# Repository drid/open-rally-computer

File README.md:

# Open Rally Computer

An open source tripmaster for navigation rallies

## Description

The Open Rally Computer (previously known as [Baja Pro](https://baja.matto.io/)) is a complete tripmaster for navigation rallies.

Some of its features are:

- Based on GPS technology
- Adjustable partial distance odometer
- Total distance odometer
- Speedometer
- Average speed
- Max speed
- Trip time
- Compass (CAP heading)
- Multiple languages and unit systems
- Firmware updates over-the-air

The main goal of this project is to achieve a widely used open-source device that can be improved over time by ourselves, the pilots behind the roadbook.

You can read a detailed writeup of the project here:

- [English version](https://matto.io/open-sourcing-the-baja-pro/)
- [Spanish version](https://matto.io/liberando-el-codigo-del-baja-pro/)

## Schematics and PCB

You can find all the necessary information for fabricating your own copy of the Open Rally Computer PCB in the [pcb](docs/pcb) and [schematics](docs/schematics) folders of this repository.

> **HELP NEEDED**: My knowledge in electronics is self-taught, so I'm sure there are quite a few improvements to be done in this department. If you know electronics and spot something that can be improved, please let me know by opening an issue.

- Previous models of this device have been fabricated at [JLCPCB](https://jlcpcb.com/) with great results and very good prices.
- The system I used to create the PCB was [EasyEDA](https://easyeda.com/). You can find files for the schematics and the PCB in their relative folders. There are also versions for Altium Designer.

> **HELP NEEDED**: I'd like to port these schematics and PCB to KiCad, so we continue with the open source spirit :)
>
> If you know your way around KiCad, I'd really appreciate some help porting this board.

The bill of materials is located in a CSV file in the [bom](docs/pcb/bom) folder. If you find a missing component, please report it by opening an issue.

## User manual

You can find a PDF version of the User Manual in the [manual](docs/manual) folder.

> **HELP NEEDED**: The user manual is currently only in Spanish and it still has a lot of Baja Pro branding that has to be changed to "Open Rally Computer". I'd really appreciate some help transcribing it to Markdown and translating it into other languages, being english the top priority right now.

## Getting Started

These instructions will allow you to compile the project in you local computer. In order to run it you will need an actual device.

### Prerequisites

This project has been developed using VSCode with the PlatformIO plugin, which is is the recommended setup.

- Install [VSCode](https://code.visualstudio.com/)
- Install the [PlatformIO plugin](https://platformio.org/install/ide?install=vscode)
- Clone this repository

```bash
git clone https://github.com/mattogodoy/open-rally-computer.git
```

### Building

To build this project you can open the directory of the repository you just downloaded in VSCode.

Once open, go to the sidebar at the left, PlatformIO -> esp32dev -> General -> Build

The required libraries are already bundled in the `lib` directory of this repo. PlatformIO will automatically try to use them.
If for some reason you are getting compilation errors because of missing libraries, you can always install them manually going to PlatformIO -> PIO Home -> Libraries.

You can find the list of necessary libraries in the file [platformio.ini](platformio.ini).

## Flashing into device

Once the project compiles correctly in your computer, you are ready to flash it into the rally computer.

1. Connect your ESP32 (DevKit or programmer) to your computer via USB.
2. Go to PlatformIO -> esp32dev -> General -> Upload
3. PlatformIO should automatically detect the serial port where your ESP32 is connected, buld the project and flash it for you.

## Contributing

Please read [CONTRIBUTING.md](CONTRIBUTING.md) for details on the process for submitting pull requests.

Also read [CODE_OF_CONDUCT.md](CODE_OF_CONDUCT.md) for details on the code of conduct for this project.

## Versioning

We use [SemVer](http://semver.org/) for versioning.

For a list of available versions, see the [tags on this repository](https://github.com/mattogodoy/open-rally-computer/tags).

## Authors

- **Matías Godoy** - [matto.io](https://matto.io/)

See also the list of [contributors](https://github.com/mattogodoy/open-rally-computer/graphs/contributors) who participated in this project.

## TO-DO

There are a few things I'd like to do in order to improve this project and its repository:

- [x] Build, upload and tag Version 1.0.0 binary as a release
- [x] Translate user manual to english
- [ ] Port the PCB files to KiCad
- [ ] Create proper documentation in GitHub Wiki
- [ ] Create Continuous Integration using GitHub Actions

## License

This project is licensed under the GPL v3 License - see the [LICENSE](LICENSE) file for details.

This is what this means:

1. Anyone can copy, modify and distribute this software.
2. If you do, you have to include the license and copyright notice with each and every distribution.
3. You can use this software privately.
4. You can use this software for commercial purposes.
5. If you build your business based on this code, you have to open-source your whole code base.
6. Any modifications of this code base MUST be distributed with the same license (GPL v3).
7. Any changes made to this code MUST be indicated on distribution.
8. This software is provided without warranty.
9. The software author or license can not be held liable for any damages inflicted by the software.

## Changelog

- **1.0.0**: Initial version
  - The complete project was open sourced, including source code, bill of materials, PCB desings and user manual.

## Contributors

- [turtle3333](https://github.com/turtle3333): User manual translation

## Forks

- [https://github.com/adamshatzkamer/open-rally-computer](https://github.com/adamshatzkamer/open-rally-computer) A fork of this project that focuses on making it easier to assemble using Adafruit Feather boards and FeatherWing accessories. This version is designed to simplify hardware selection and wiring, making it more accessible for beginners and hobbyists.

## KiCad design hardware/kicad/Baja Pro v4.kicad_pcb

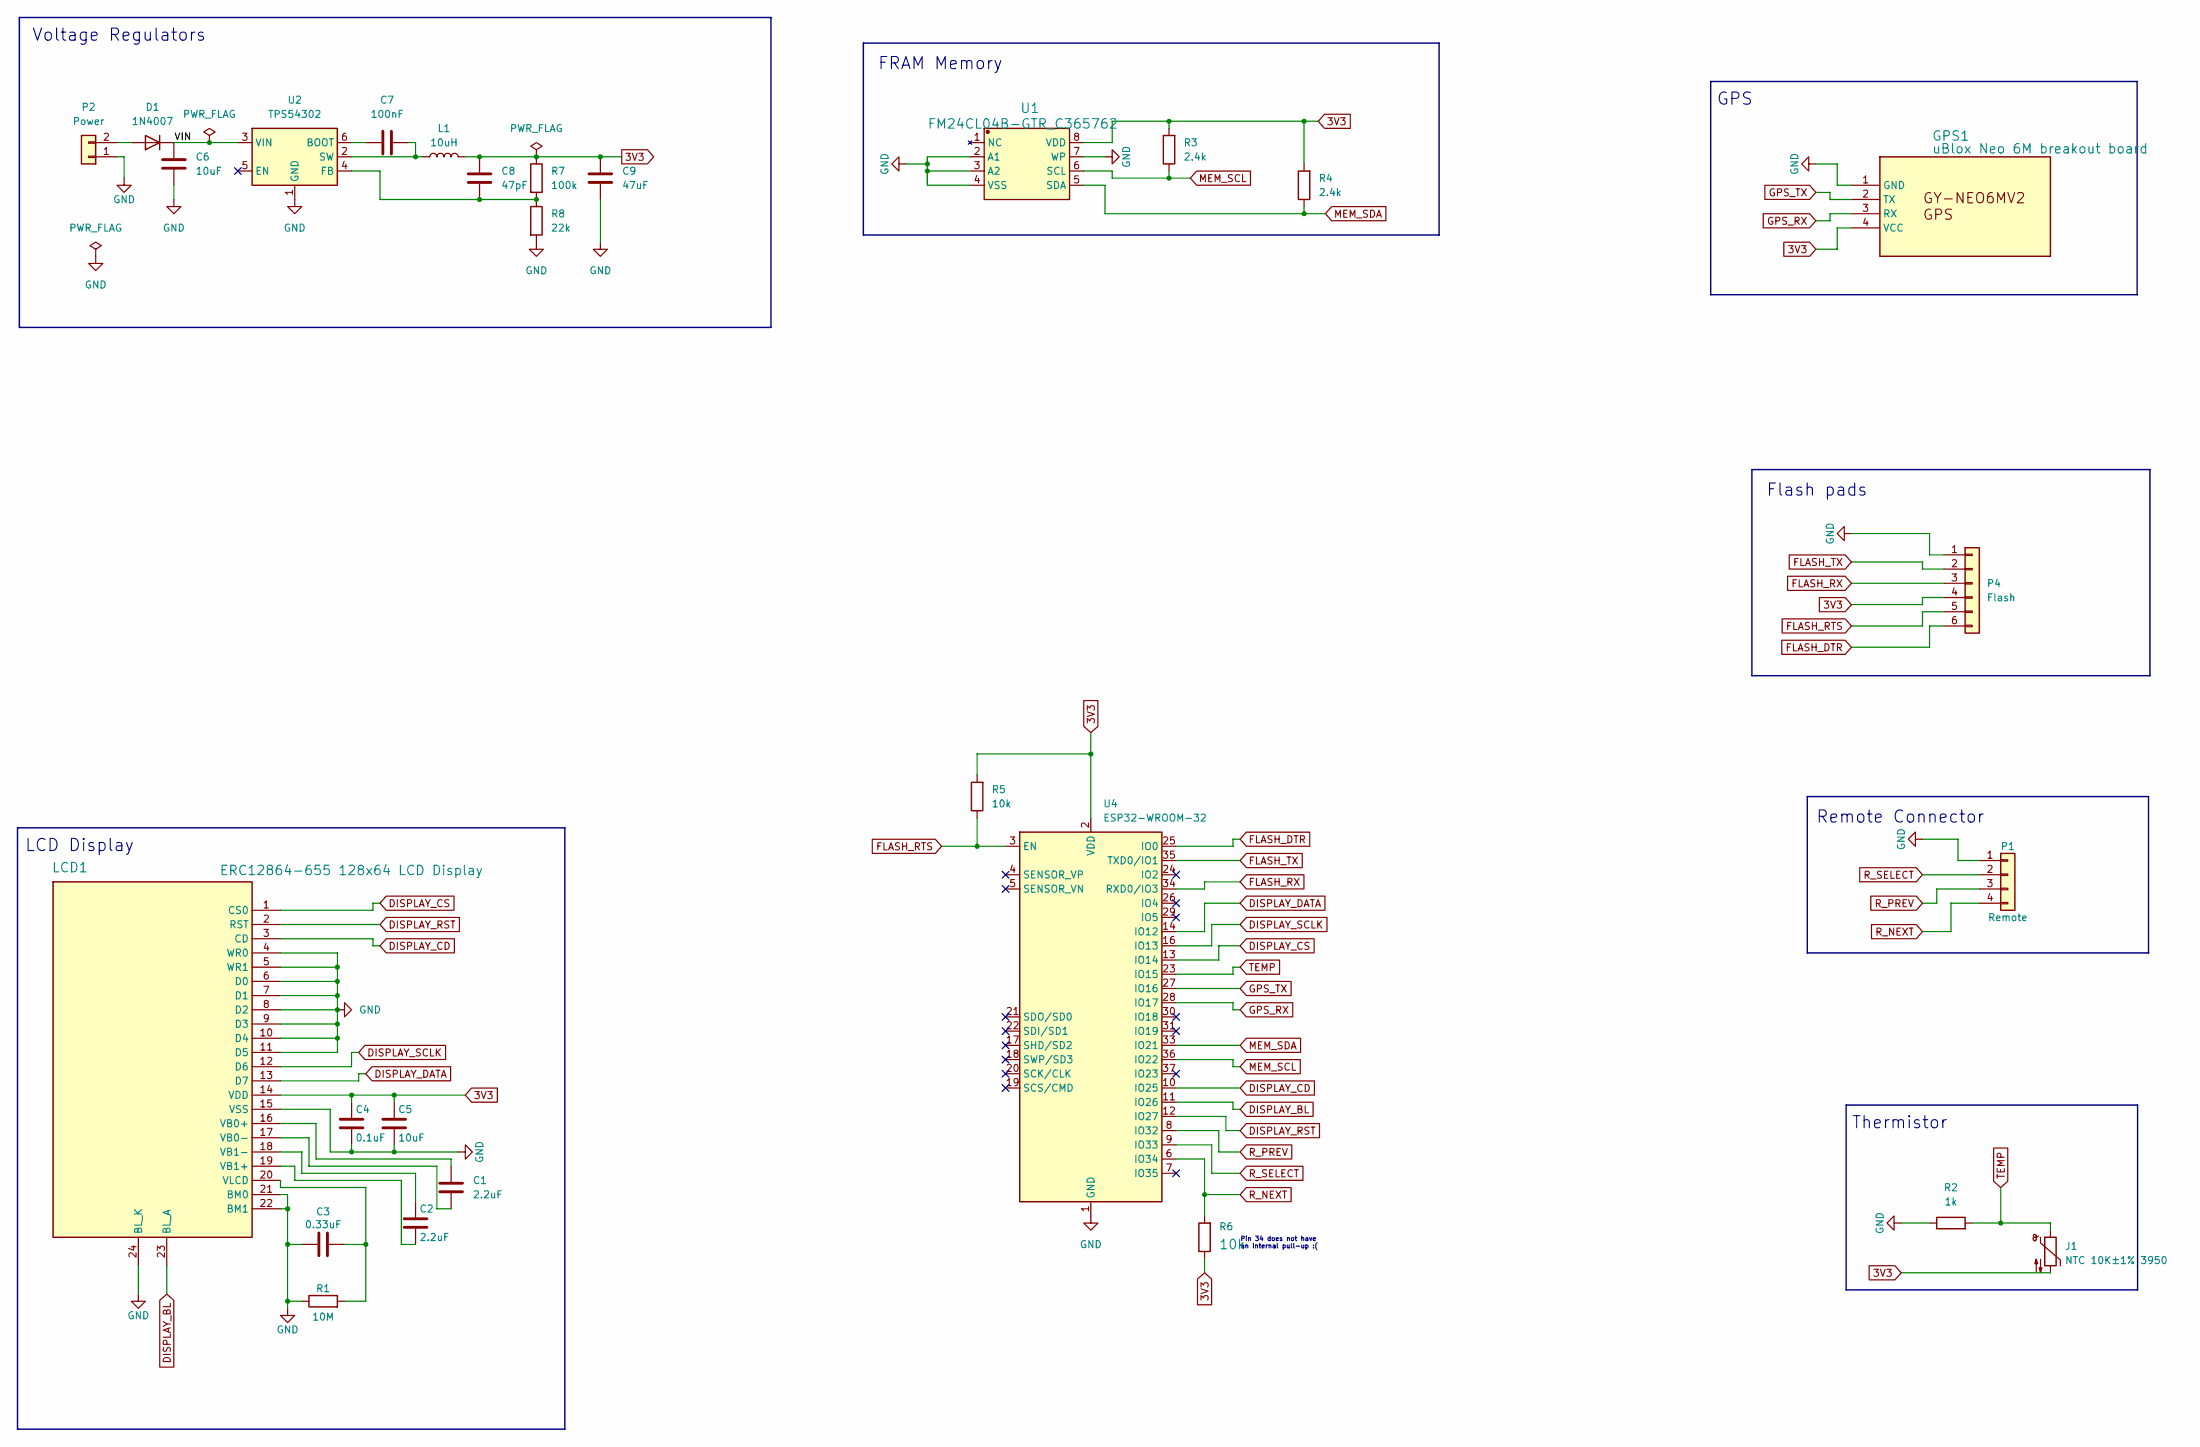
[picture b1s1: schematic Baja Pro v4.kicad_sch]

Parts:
C1, C2: 2.2uF; C_1206_3216Metric_Pad1.33x1.80mm_HandSolder
C3: 0.33uF; C_1206_3216Metric_Pad1.33x1.80mm_HandSolder
C4: 0.1uF; C_1206_3216Metric_Pad1.33x1.80mm_HandSolder
C5: 10uF; C_1206_3216Metric_Pad1.33x1.80mm_HandSolder
C6: 10uF; C_1210_3225Metric_Pad1.33x2.70mm_HandSolder; PartNumber CL32A106KBJNNNE
C7: 100nF; C_0805_2012Metric_Pad1.18x1.45mm_HandSolder; PartNumber C0805C104M5RACTU
C8: 47pF; C_0603_1608Metric_Pad1.08x0.95mm_HandSolder
C9: 47uF; C_1210_3225Metric_Pad1.33x2.70mm_HandSolder; PartNumber GRM32ER61C476KE15L
D1: 1N4007; D_SOD-123F
GPS1: uBlox Neo 6M breakout board; GY-NEO6MV2; Manufacturer Part GY-NEO6MV2
J1: NTC 10K±1% 3950; R_0805_2012Metric_Pad1.20x1.40mm_HandSolder
L1: 10uH; L_Bourns_SRP5030T; PartNumber SRP5030T-5R6M
LCD1: ERC12864-655 128x64 LCD Display; ERC12864-655; Manufacturer Part ERC12864-655
P1: Remote; JST_XH_S4B-XH-A_1x04_P2.50mm_Horizontal
P2: Power; JST_XH_S2B-XH-A_1x02_P2.50mm_Horizontal
P4: Flash; PinHeader_1x06_P2.54mm_Vertical
R1: 10M; R_1206_3216Metric_Pad1.30x1.75mm_HandSolder
R2: 1k; R_1206_3216Metric_Pad1.30x1.75mm_HandSolder
R3, R4: 2.4k; R_1206_3216Metric_Pad1.30x1.75mm_HandSolder
R5, R6: 10k; R_1206_3216Metric_Pad1.30x1.75mm_HandSolder
R7: 100k; R_0603_1608Metric_Pad0.98x0.95mm_HandSolder; PartNumber CRCW0604100KFKED
R8: 22k; R_0603_1608Metric_Pad0.98x0.95mm_HandSolder; PartNumber RC0603FR-0722KL
U1: FM24CL04B-GTR_C365762; SOIC-8_3.9x4.9mm_P1.27mm; Manufacturer Part FM24CL04B-GTR
U2: TPS54302; SOT-23-6; PartNumber TPS54302DDCR
U4: ESP32-WROOM-32

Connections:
3V3: C4.1, C5.1, C8.1, C9.1, GPS1.4 (VCC), J1.2, L1.2, LCD1.14 (VDD), P4.4, R3.2, R4.2, R5.2, R6.1, R7.1, U1.8 (VDD), U4.2 (VDD)
/VIN: C6.1, D1.1 (K), U2.3 (VIN)
DISPLAY_BL: LCD1.23 (BL_A), U4.11 (IO26)
DISPLAY_CD: LCD1.3 (CD), U4.10 (IO25)
DISPLAY_CS: LCD1.1 (CS0), U4.13 (IO14)
DISPLAY_DATA: LCD1.13 (D7), U4.14 (IO12)
DISPLAY_RST: LCD1.2 (RST), U4.12 (IO27)
DISPLAY_SCLK: LCD1.12 (D6), U4.16 (IO13)
FLASH_DTR: P4.6, U4.25 (IO0)
FLASH_RTS: P4.5, R5.1, U4.3 (EN)
FLASH_RX: P4.3, U4.34 (RXD0/IO3)
FLASH_TX: P4.2, U4.35 (TXD0/IO1)
GND: C3.1, C4.2, C5.2, C6.2, C9.2, GPS1.1 (GND), LCD1.4 (WR0), LCD1.5 (WR1), LCD1.6 (D0), LCD1.7 (D1), LCD1.8 (D2), LCD1.9 (D3), LCD1.10 (D4), LCD1.11 (D5), LCD1.15 (VSS), LCD1.21 (BM0), LCD1.22 (BM1), LCD1.24 (BL_K), P1.1, P2.1, P4.1, R1.1, R2.1, R8.2, U1.2 (A1), U1.3 (A2), U1.4 (VSS), U1.7 (WP), U2.1 (GND), U4.1 (GND), U4.15 (GND), U4.38 (GND), U4.39 (GND)
GPS_RX: GPS1.3 (RX), U4.28 (IO17)
GPS_TX: GPS1.2 (TX), U4.27 (IO16)
MEM_SCL: R3.1, U1.6 (SCL), U4.36 (IO22)
MEM_SDA: R4.1, U1.5 (SDA), U4.33 (IO21)
unnamed: D1.2 (A), P2.2
unnamed: C1.2, LCD1.16 (VB0+)
unnamed: C1.1, LCD1.17 (VB0-)
unnamed: C2.2, LCD1.19 (VB1+)
unnamed: C2.1, LCD1.18 (VB1-)
unnamed: C3.2, LCD1.20 (VLCD), R1.2
unnamed: C7.1, U2.6 (BOOT)
unnamed: C8.2, R7.2, R8.1, U2.4 (FB)
unnamed: C7.2, L1.1, U2.2 (SW)
R_NEXT: P1.4, R6.2, U4.6 (IO34)
R_PREV: P1.3, U4.8 (IO32)
R_SELECT: P1.2, U4.9 (IO33)
TEMP: J1.1, R2.2, U4.23 (IO15)

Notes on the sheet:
FRAM Memory
Thermistor
GPS
Pin 34 does not have an internal pull-up :(
Flash pads
Voltage Regulators
LCD Display
Remote Connector

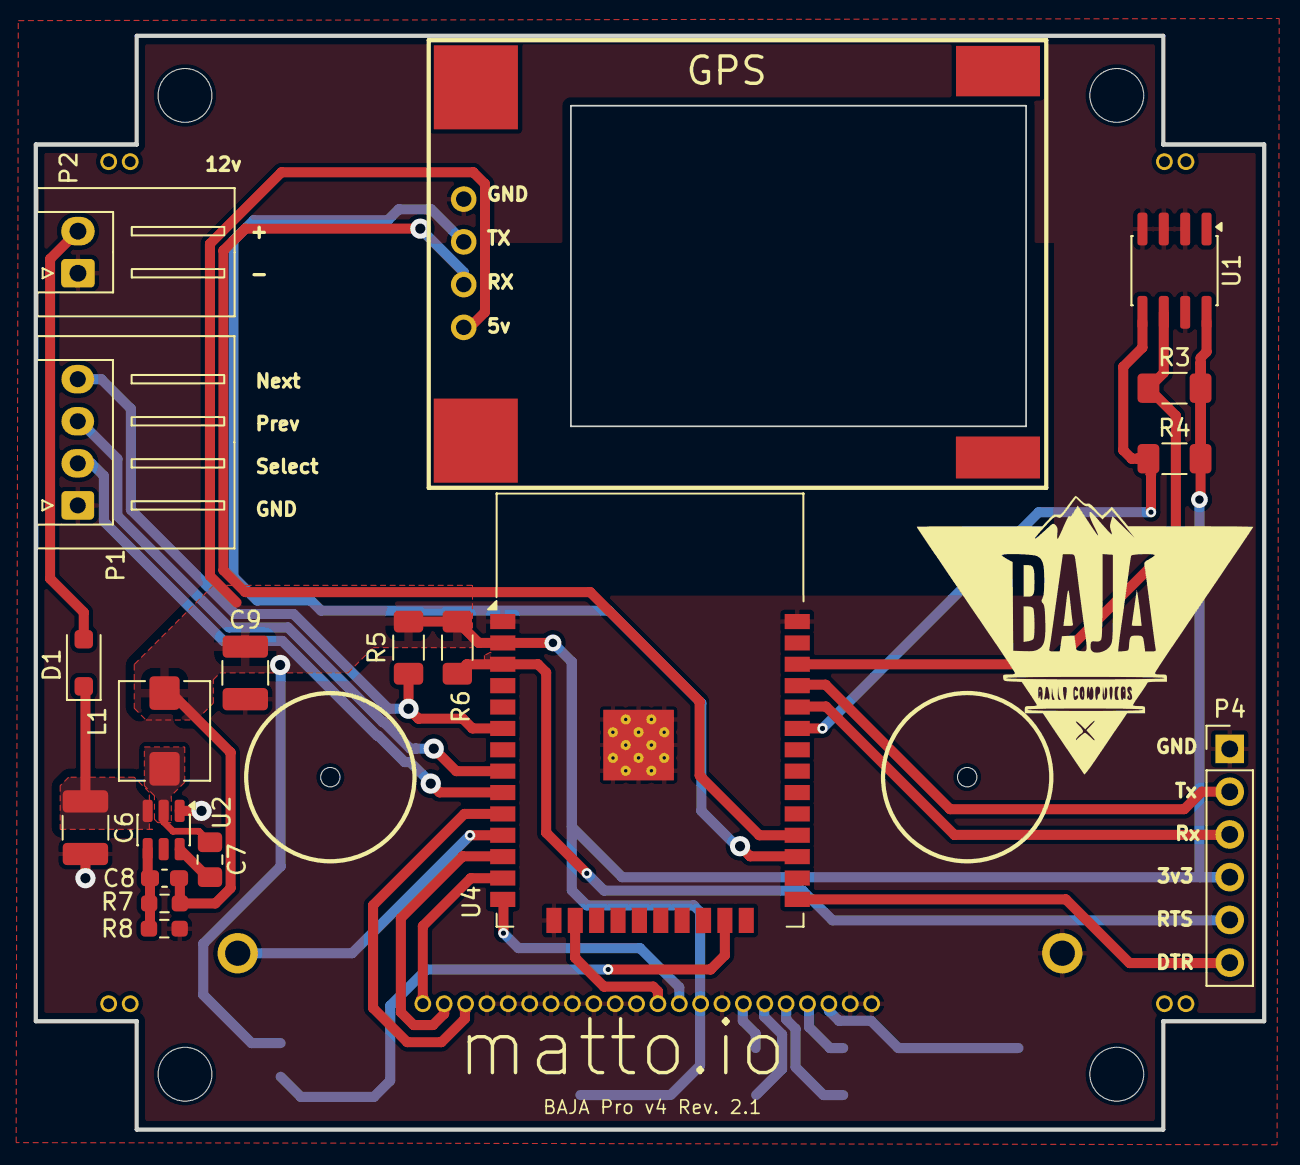
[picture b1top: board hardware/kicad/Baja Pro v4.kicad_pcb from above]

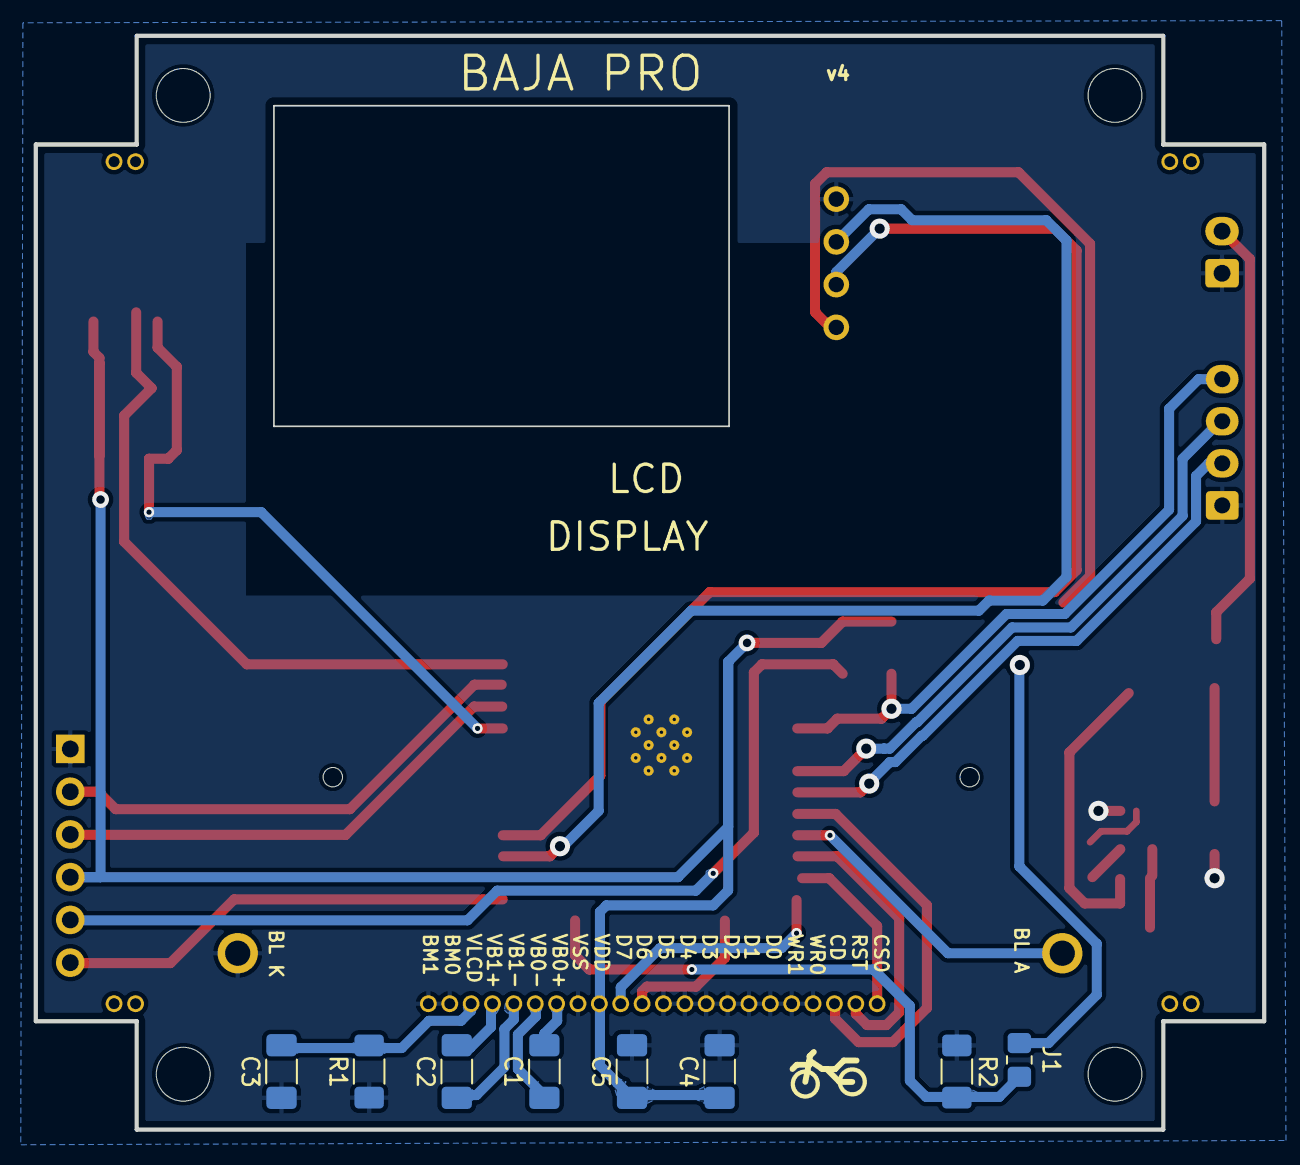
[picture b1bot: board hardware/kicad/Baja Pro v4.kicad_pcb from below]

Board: 2 copper layers, 73.0 x 65.0 mm, 28 parts (9 on the bottom side), 30 nets.

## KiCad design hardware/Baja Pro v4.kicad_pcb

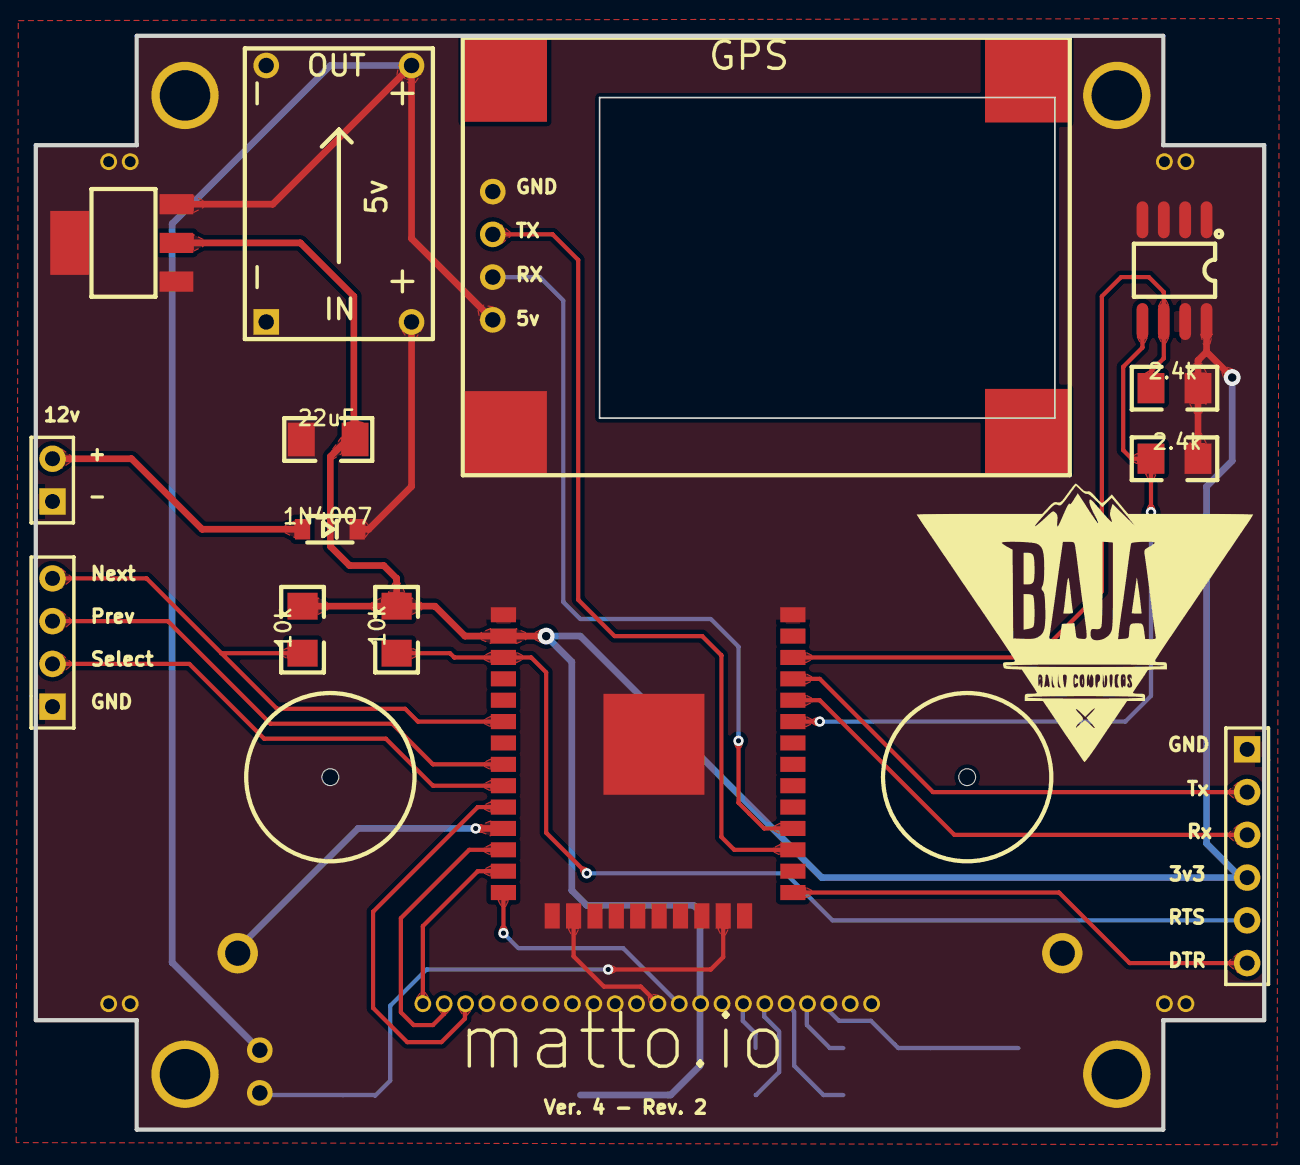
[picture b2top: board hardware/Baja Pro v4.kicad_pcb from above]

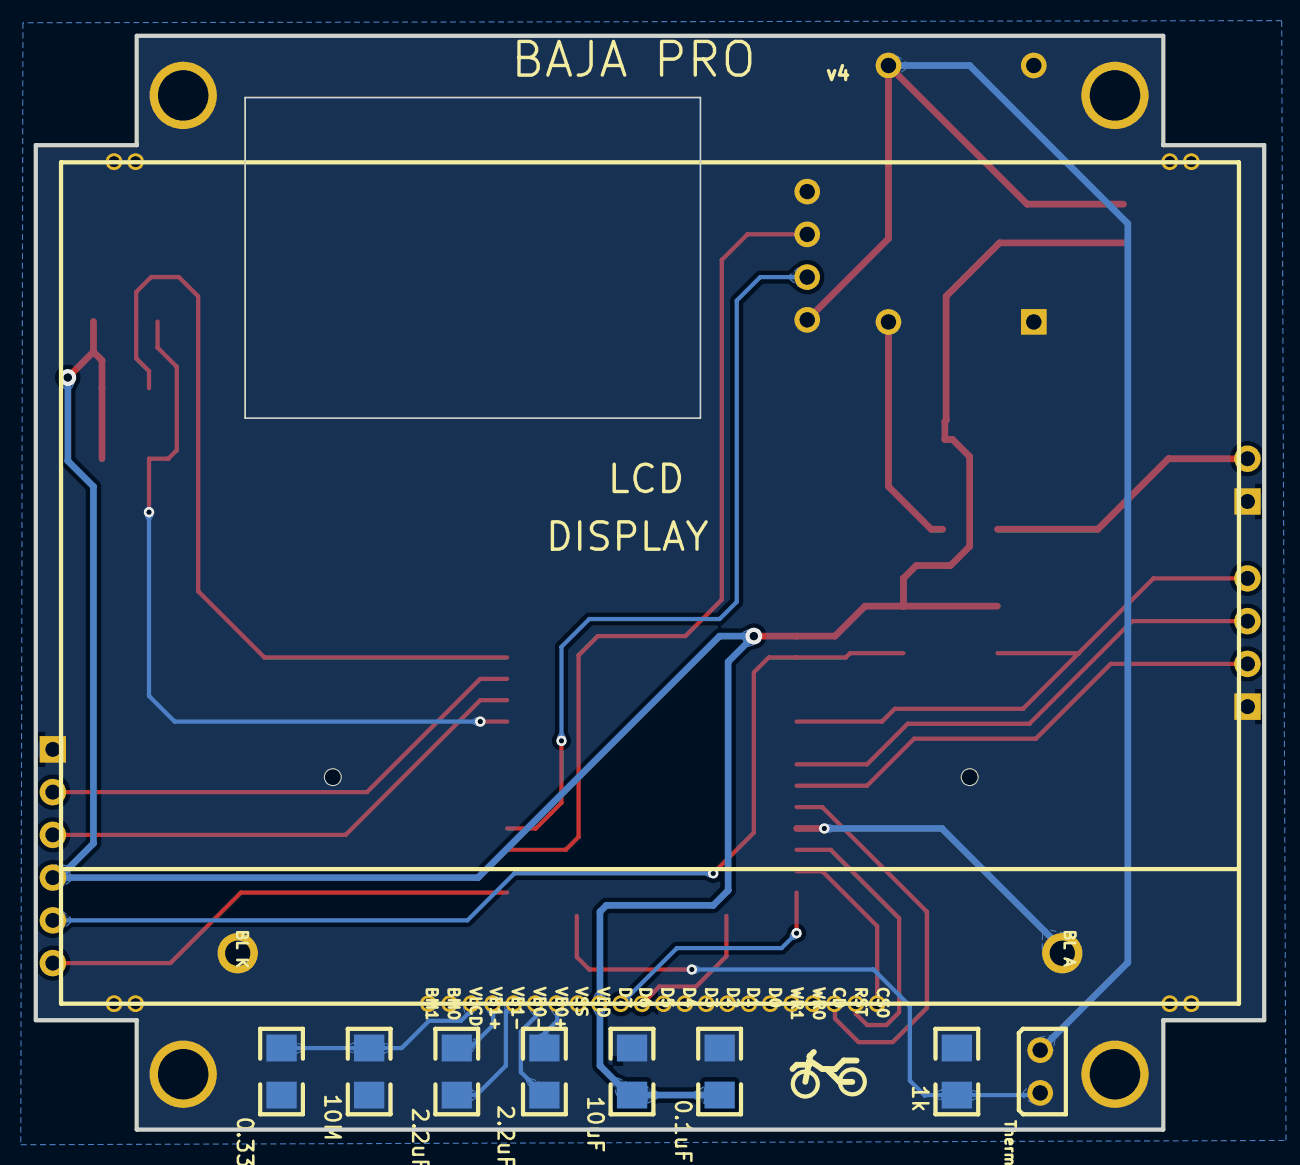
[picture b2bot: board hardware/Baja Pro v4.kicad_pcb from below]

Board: 2 copper layers, 73.0 x 65.0 mm, 29 parts (9 on the bottom side), 28 nets.

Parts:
C1, C2: 2.2uF; 1206
C3: 0.33uF; 1206
C4: 0.1uF; 1206
C5: 10uF; 1206
C6: 22uF; 1206
D1: 1N4007; SOD-123F
GPS1: uBlox Neo 6M breakout board; GY-NEO6MV2
Hole_gge526: Hole_gge526
Hole_gge527: Hole_gge527
LCD1: ERC12864-655 128x64 LCD Display; ERC12864-655
P1: Header-Female-2.54_1x4; HDR-4X1/2.54
P2: Header-Female-2.54_1x2; HDR-1X2/2.54
P4: Header-Female-2.54_1x6; HDR-6X1/2.54
Pad_gge522: Pad_gge522
Pad_gge523: Pad_gge523
Pad_gge524: Pad_gge524
Pad_gge525: Pad_gge525
R1: 10M; 1206
R2: 1k; 1206
R3, R4: 2.4k; 1206
R5, R6: 10k; 1206
U1: FM24CL04B-GTR_C365762; SOIC-8_150MIL
U2: DC-DC stepdown; DC-DC STEPDOWN
U3: AMS1117-3.3; SOT-223
U4: Thermistor; THERMISTOR-PCB
X1: ESP32_WROOM32; WROOM32

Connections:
3V3: C4.1, C5.1, C6.2, LCD1.14, P4.4, R3.2, R4.2, R5.2, R6.1, U1.8, U3.2, X1.2
5V: GPS1.4, U2.3, U3.3, U4.1
C1_1: C1.1, LCD1.17
C1_2: C1.2, LCD1.16
C2_1: C2.1, LCD1.18
C2_2: C2.2, LCD1.19
C3_2: C3.2, LCD1.20, R1.2
D1_1: D1.1, P2.2
D1_2: D1.2, U2.2
DISPLAY_BL: LCD1.23, X1.11
DISPLAY_CD: LCD1.3, X1.10
DISPLAY_CS: LCD1.1, X1.13
DISPLAY_DATA: LCD1.13, X1.14
DISPLAY_RST: LCD1.2, X1.12
DISPLAY_SCLK: LCD1.12, X1.16
FLASH_DTR: P4.6, X1.25
FLASH_RTS: P4.5, R5.1, X1.3
FLASH_RX: P4.3, X1.34
FLASH_TX: P4.2, X1.35
GND: C3.1, C4.2, C5.2, C6.1, GPS1.1, LCD1.4, LCD1.5, LCD1.6, LCD1.7, LCD1.8, LCD1.9, LCD1.10, LCD1.11, LCD1.15, LCD1.21, LCD1.22, LCD1.24, P1.1, P2.1, P4.1, R1.1, R2.1, U1.1, U1.2, U1.3, U1.4, U1.7, U2.1, U2.4, U3.1, X1.1, X1.15, X1.38, X1.P$1
GPS_RX: GPS1.3, X1.28
GPS_TX: GPS1.2, X1.27
MEM_SCL: R3.1, U1.6, X1.36
MEM_SDA: R4.1, U1.5, X1.33
R_NEXT: P1.4, R6.2, X1.6
R_PREV: P1.3, X1.8
R_SELECT: P1.2, X1.9
TEMP: R2.2, U4.2, X1.23

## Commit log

2026-02-05 Initial import to KiCAD 8
2026-02-06 Update to KiCAD9 Create missing symbols Replace symbols with KiCAD symbols Link symbols with footprints
2026-02-11 Move kicad files to kicad folder
2026-02-11 Implement on board DCDC converter Run on 3.3V Replace thermistor with SMD one Change cable connectors to JST Rearrange tracks to help WiFi antenna clearance
2026-02-11 Add part numbers Generate BOM Generate HTML assembly

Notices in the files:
hardware/kicad/Baja Pro v4.kicad_pcb:
GPL-3.0
